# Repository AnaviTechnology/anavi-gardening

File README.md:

# ANAVI Gardening uHAT

iANAVI Gardening uHAT is a low-cost, open source Raspberry Pi add-on board that helps you develop smart solutions for monitoring and growing plants.

ANAVI Gardening uHAT supports multiple sensors for soil moisture, temperature, humidity, barometric pressure, and light. No soldering is required. Getting started is easy. You just plug it into a Raspberry Pi with your bare hands (no tools needed) and follow the steps from the user manual.

For more details please visit https://anavi.technology/ and https://www.crowdsupply.com/anavi-technology/anavi-gardening-uhat

## Features

* Slots for up to two capacitive soil moisture sensors
* Slot for waterproof temperature sensor
* Slots for up to two plug-and-play I2C sensors
* UART pins for serial communication
* GPIO pins for controlling irrigation systems and peripherals
* Green and red indication LEDs
* Microchip MCP3002 Analog-to-Digital Converter (ADC)
* Follows uHAT mechanical specification with a valid ID EEPROM
* Excellent software support, documentation, and open source examples

# Safety Guide

## English

### Warnings

* This product shall only be connected to a compatible Raspberry Pi.
      
### Instructions for safe use

* Do not expose this product to water or moisture, and do not place it on a conductive surface whilst in operation.
* Do not expose this product to heat from any source; it is designed for reliable operation at normal room temperatures.
* Take care while handling this product to avoid mechanical or electrical damage to the printed circuit board and connectors.
* Avoid handling this product while it is powered. Only handle by the edges to minimize the risk of electrostatic discharge damage.
      
## Deutsch

### Achtung

* Dieses Produkt darf nur mit einem kompatiblen Raspberry Pi verbunden werden.
      
### Anweisungen für die sichere Verwendung

* Setzen Sie dieses Produkt nicht Wasser oder Feuchtigkeit aus und stellen Sie es während des Betriebs nicht auf eine leitfähige Oberfläche.
* Setzen Sie dieses Produkt keiner Wärmequelle aus. Es ist für einen zuverlässigen Betrieb bei normalen Raumtemperaturen ausgelegt.
* Seien Sie vorsichtig beim Umgang mit diesem Produkt, um mechanische oder elektrische Schäden an der Leiterplatte und den Anschlüssen zu vermeiden.
* Vermeiden Sie die Handhabung dieses Produkts während der Stromversorgung. Produkt nur an den Rändern anfassen, um das Risiko von elektrostatischen Entladungsschäden zu minimieren.

# License

The project is released under the [Creative Commons Attribution-ShareAlike 4.0 International (CC BY-SA 4.0)](https://creativecommons.org/licenses/by-sa/4.0/).

Note: This is a human-readable summary of (and not a substitute for) the [license](https://creativecommons.org/licenses/by-sa/4.0/legalcode).

You are free to:

Share — copy and redistribute the material in any medium or format Adapt — remix, transform, and build upon the material for any purpose, even commercially. The licensor cannot revoke these freedoms as long as you follow the license terms. Under the following terms:

Attribution — You must give appropriate credit, provide a link to the license, and indicate if changes were made. You may do so in any reasonable manner, but not in any way that suggests the licensor endorses you or your use. ShareAlike — If you remix, transform, or build upon the material, you must distribute your contributions under the same license as the original. No additional restrictions — You may not apply legal terms or technological measures that legally restrict others from doing anything the license permits. Notices:

You do not have to comply with the license for elements of the material in the public domain or where your use is permitted by an applicable exception or limitation. No warranties are given. The license may not give you all of the permissions necessary for your intended use. For example, other rights such as publicity, privacy, or moral rights may limit how you use the material.

You will have to provide a link to the original creator of the project http://www.anavi.technology on any documentation or website.

Credit can be attributed through a link to the creator website: http://www.anavi.technology

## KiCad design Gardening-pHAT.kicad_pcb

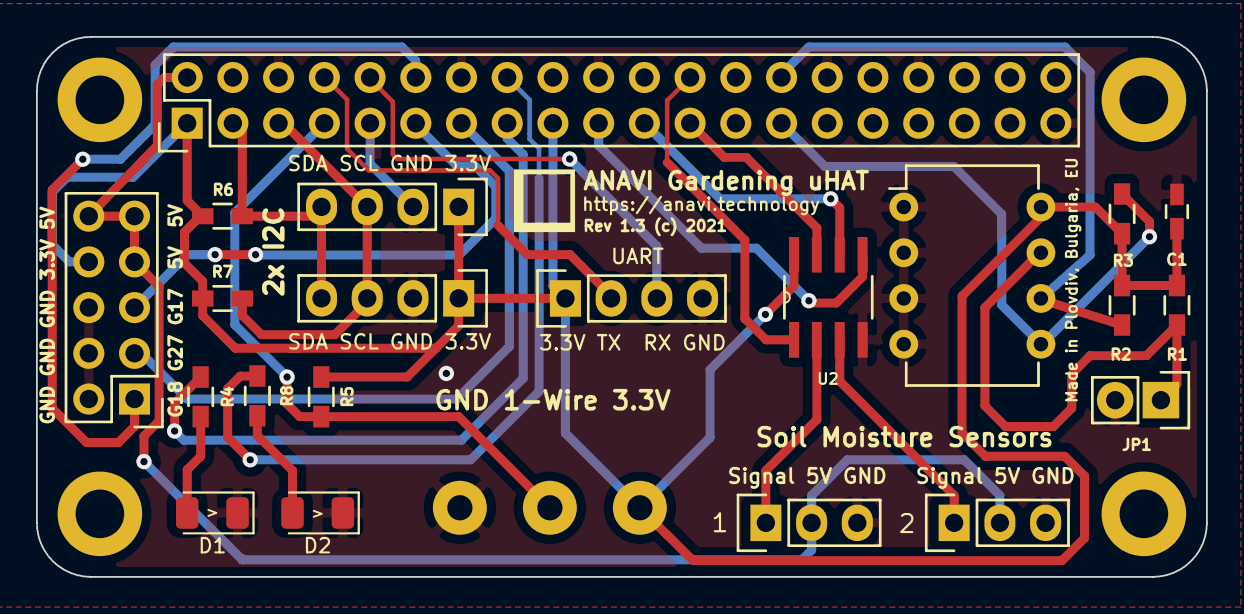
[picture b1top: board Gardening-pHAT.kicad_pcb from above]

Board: 2 copper layers, 65.0 x 30.0 mm, 26 parts (0 on the bottom side), 24 nets.

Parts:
1, 2: CONN_01X03; Pin_Header_Straight_1x03
C1: 0.1; C_0603_HandSoldering
D1: KP-3216EC; LED_1206_3216Metric
D2: KP-3216SGC; LED_1206_3216Metric
JP1: JUMPER; Pin_Header_Straight_1x02
P1: CONN_01X03; KLEMA_1x3
P4: CONN_02X05; Pin_Header_Straight_2x05
R1: 1K; R_0603_HandSoldering
R2, R3, R5, R6, R7: 4.7K; R_0603_HandSoldering
R4, R8: 270R; R_0603_HandSoldering
RASP_CONN1: Raspberry_PI; Pin_Header_Straight_2x20
REF1, REF2, REF3, REF4: MountingHole_2.7mm_M2.5_DIN965_Pad
SENS1, SENS2: I2C_SENS_1; Pin_Header_Straight_1x04
U1: CAT24C32WI-GT3; DIP-8_W7.62mm
U2: MCP3002; SOIC127P600X175-8N
UART: CONN_01X04; Pin_Header_Straight_1x04

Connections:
+3V3: C1.1, P1.3, P4.8, R1.1, R2.1, R3.1, R5.1, R6.1, R7.1, RASP_CONN1.1, RASP_CONN1.17, SENS1.1, SENS2.1, U1.8, U2.8, UART.1
+5V: 1.2, 2.2, P4.7, P4.9, P4.10, RASP_CONN1.2, RASP_CONN1.4
/RXD: RASP_CONN1.10, UART.3
/TXD: RASP_CONN1.8, UART.2
GND: 1.3, 2.3, C1.2, D1.1, D2.1, JP1.2, P1.1, P4.2, P4.4, P4.6, RASP_CONN1.6, RASP_CONN1.9, RASP_CONN1.14, RASP_CONN1.20, RASP_CONN1.25, RASP_CONN1.30, RASP_CONN1.34, RASP_CONN1.39, SENS1.2, SENS2.2, U1.1, U1.2, U1.3, U1.4, U2.4, UART.4
unnamed: D1.2, R4.1
unnamed: D2.2, R8.1
unnamed: JP1.1, R1.2, U1.7
unnamed: P1.2, R5.2, RASP_CONN1.7
unnamed: 2.1, U2.3
unnamed: 1.1, U2.2
unnamed: P4.1, RASP_CONN1.12
unnamed: P4.3, RASP_CONN1.13
unnamed: P4.5, RASP_CONN1.11
unnamed: R2.2, RASP_CONN1.28, U1.6
unnamed: R3.2, RASP_CONN1.27, U1.5
unnamed: R4.2, RASP_CONN1.15
unnamed: R6.2, RASP_CONN1.3, SENS1.4, SENS2.4
unnamed: R7.2, RASP_CONN1.5, SENS1.3, SENS2.3
unnamed: R8.2, RASP_CONN1.16
unnamed: RASP_CONN1.19, U2.5
unnamed: RASP_CONN1.21, U2.6
unnamed: RASP_CONN1.23, U2.7
unnamed: RASP_CONN1.24, U2.1

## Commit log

2017-04-07 ANAVI Gardening pHAT
    Initial commit
2017-04-07 Remove one I2C slot and change labels
    Leave only two I2C slots to ensure that there is
    enough space for the labels. Fix wiring issues.
2017-04-07 Gardening-pHAT.kicad_pcb: Move labels
2017-04-07 Gardening-pHAT.kicad_pcb: Replace labels
    Replace "Analog" with "Signal" and adjust the
    position of the labels.
2017-04-09 Gardening-pHAT.sch: Hide text
2017-04-09 Gardening-pHAT.kicad_pcb: Change output directory
2017-04-10 Fix routing
2017-04-10 Update fill zones
2017-04-10 Update routing again
2017-04-10 Add junction between 5V pins on the header
2017-04-10 Gardening-pHAT.kicad_pcb: Hide UART connector text
2017-04-21 Revision 1.1
    Revision 1.1 contains these improvements:
    * Fixed 1-wire connection for DS18B20 sensor
    * Swap GND and 3.3V for analog sensors
    * Update text labels
2017-04-24 Gardening-pHAT.kicad_pcb: rev 1.1
2017-05-01 Control 3.3V to sensors through GPIO
    Connect the 3.3V of the soil moisture sensors
    to GPIO5 and GPIO6 of Raspberry Pi. This way
    the sensors will be enabled only during
    measurement and their life will be significantly
    increased.
2021-05-07 Gardening-pHAT.*: Remap symbols
    Remap symbols for newer KiCad version.
2021-05-11 Gardening-pHAT: Update tracks
    Update tracks and labels.
2021-07-20 Add fabrication labels for assemly
    Create additional labels on the fabrication layer to help with
    the SMT assembly of the PCB.
2021-09-06 README.md: CC BY-SA 4.0
    Use C BY-SA 4.0 license and update notes.
2021-12-29 README.md: Add safety guide
    Add a new section for safety guide in English and German.

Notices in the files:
Gardening-pHAT.kicad_pcb:
Rev 1.3 (c) 2021
